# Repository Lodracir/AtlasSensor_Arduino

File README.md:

# AtlasSensor_Arduino
Atlas Sensor Arduino Program

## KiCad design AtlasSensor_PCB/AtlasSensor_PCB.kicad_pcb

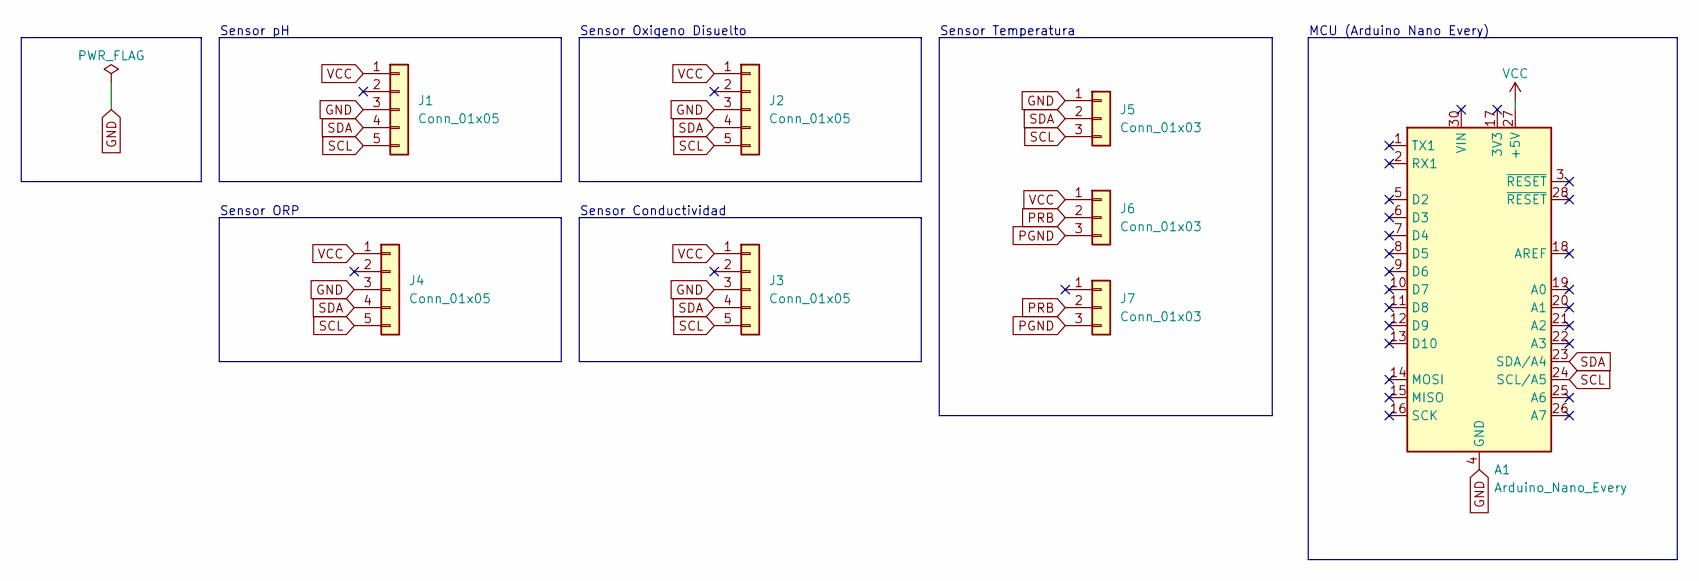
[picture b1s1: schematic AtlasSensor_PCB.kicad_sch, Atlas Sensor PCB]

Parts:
A1: Arduino_Nano_Every; Arduino_Nano
J1, J2, J3, J4: Conn_01x05; PinSocket_1x05_P2.54mm_Horizontal
J5, J6, J7: Conn_01x03; PinSocket_1x03_P2.54mm_Vertical

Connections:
GND: A1.4 (GND), A1.29 (GND), J1.3, J2.3, J3.3, J4.3, J5.1
PGND: J6.3, J7.3
PRB: J6.2, J7.2
SCL: A1.24 (SCL/A5), J1.5, J2.5, J3.5, J4.5, J5.3
SDA: A1.23 (SDA/A4), J1.4, J2.4, J3.4, J4.4, J5.2
VCC: A1.27 (+5V), J1.1, J2.1, J3.1, J4.1, J6.1

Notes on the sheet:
Sensor ORP
Sensor Oxigeno Disuelto
MCU (Arduino Nano Every)
Sensor Temperatura
Sensor Conductividad
Sensor pH

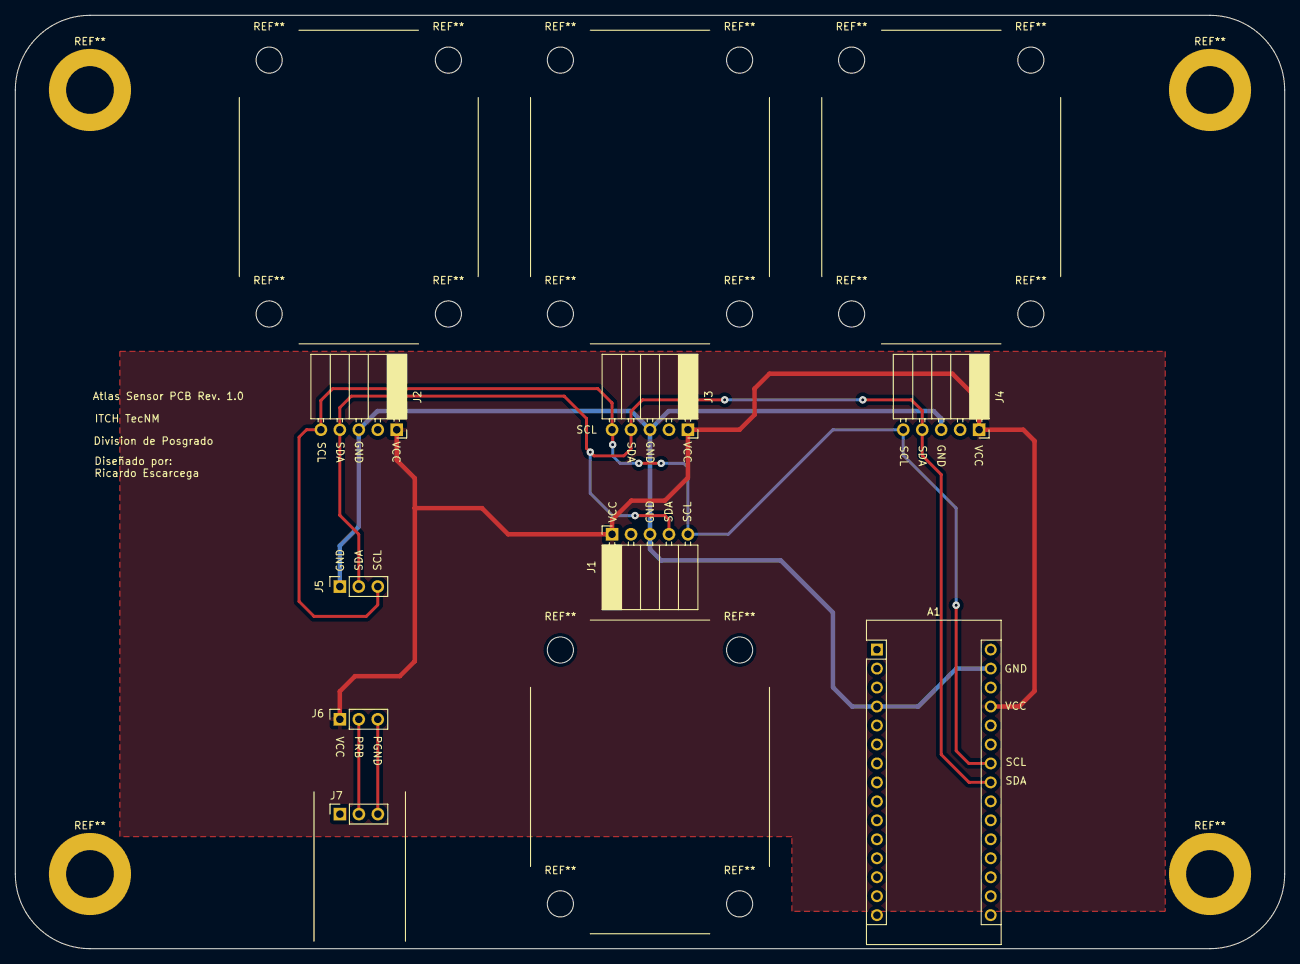
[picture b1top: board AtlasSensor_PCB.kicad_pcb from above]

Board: 2 copper layers, 170.0 x 125.0 mm, 8 parts (0 on the bottom side), 6 nets.

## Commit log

2022-06-21 Added main arduino file and libraries for Atlas Sensors (V1.0)
2022-06-30 New folder created to store Arduino files
2022-06-30 Added PCB Files
2022-07-19 Deleted Arduino INO Project
2022-07-19 Added now Arduino files usiong Platform IO
2022-07-19 Added Demo Program
2022-08-18 Updated AtlasSensor Class
2022-08-18 Improved code and libreries
